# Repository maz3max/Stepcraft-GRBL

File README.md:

# Stepcraft-GRBL
Arduino Uno Shield for Stepcraft GRBL Controller

This is a shield to control STEPCRAFT mills via the LPT port.

(it could be easily modified to work without the LPT module directly plugged into the X1 socket)

An Arduino UNO is used with GRBL firmware and this shield.

The build option USE_SPINDLE_DIR_AS_ENABLE_PIN is needed for GRBL to work with this shield.

It works like a charm on the STEPCRAFT-2/840 with HF500 Spindle attached.

Created with KiCAD, pcb2gcodeGUI and milled on the STEPCRAFT mill itself.

The copyrights of the uploaded manuals are owned by STEPCRAFT.

http://www.netz39.de/

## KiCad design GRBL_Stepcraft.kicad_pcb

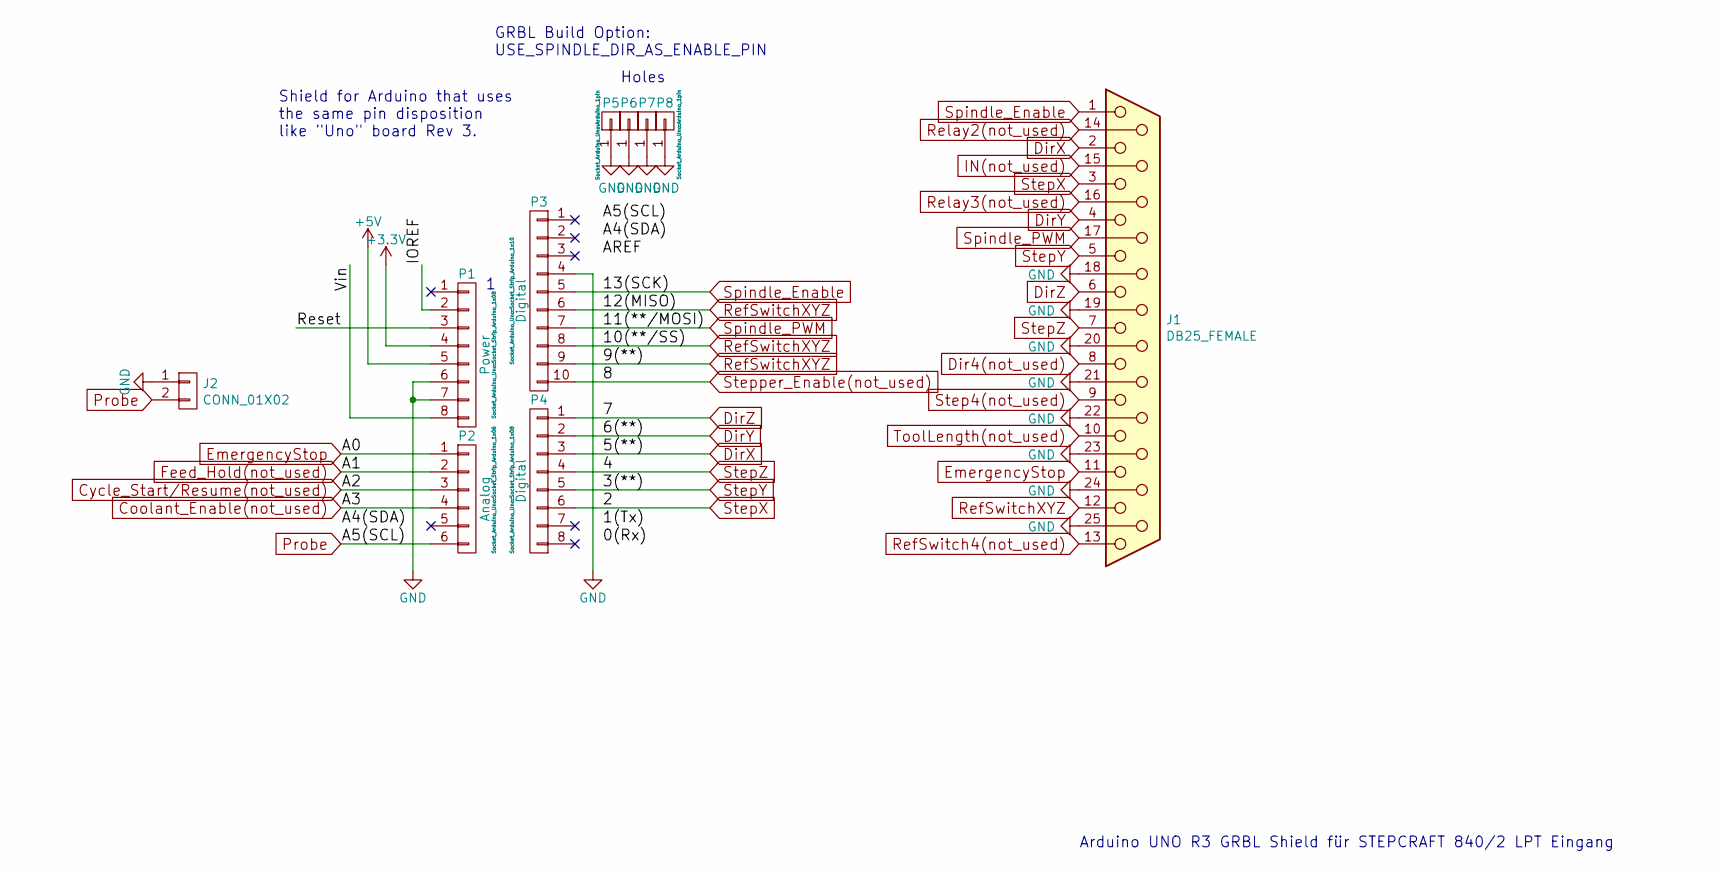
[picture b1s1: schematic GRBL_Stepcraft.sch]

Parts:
J1: DB25_FEMALE; DB25FC
J2: CONN_01X02; Pin_Header_Straight_1x02_Pitch2.54mm
P1: Power; Socket_Strip_Arduino_1x08
P2: Analog; Socket_Strip_Arduino_1x06
P3: Digital; Socket_Strip_Arduino_1x10
P4: Digital; Socket_Strip_Arduino_1x08
P5, P6, P7, P8: CONN_01X01; Arduino_1pin

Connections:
+3V3: P1.4
+5V: P1.5
/IOREF: P1.2
/Reset: P1.3
/Vin: P1.8
Coolant_Enable(not_used): P2.4
Cycle_Start/Resume(not_used): P2.3
Dir4(not_used): J1.8
DirX: J1.2, P4.3
DirY: J1.4, P4.2
DirZ: J1.6, P4.1
EmergencyStop: J1.11, P2.1
Feed_Hold(not_used): P2.2
GND: J1.18, J1.19, J1.20, J1.21, J1.22, J1.23, J1.24, J1.25, J2.1, P1.6, P1.7, P3.4, P5.1, P6.1, P7.1, P8.1
IN(not_used): J1.15
Probe: J2.2, P2.6
RefSwitch4(not_used): J1.13
RefSwitchXYZ: J1.12, P3.6, P3.8, P3.9
Relay2(not_used): J1.14
Relay3(not_used): J1.16
Spindle_Enable: J1.1, P3.5
Spindle_PWM: J1.17, P3.7
Step4(not_used): J1.9
StepX: J1.3, P4.6
StepY: J1.5, P4.5
StepZ: J1.7, P4.4
Stepper_Enable(not_used): P3.10
ToolLength(not_used): J1.10

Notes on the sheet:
Holes
Shield for Arduino that uses the same pin disposition like "Uno" board Rev 3.
GRBL Build Option: USE_SPINDLE_DIR_AS_ENABLE_PIN
Arduino UNO R3 GRBL Shield für STEPCRAFT 840/2 LPT Eingang

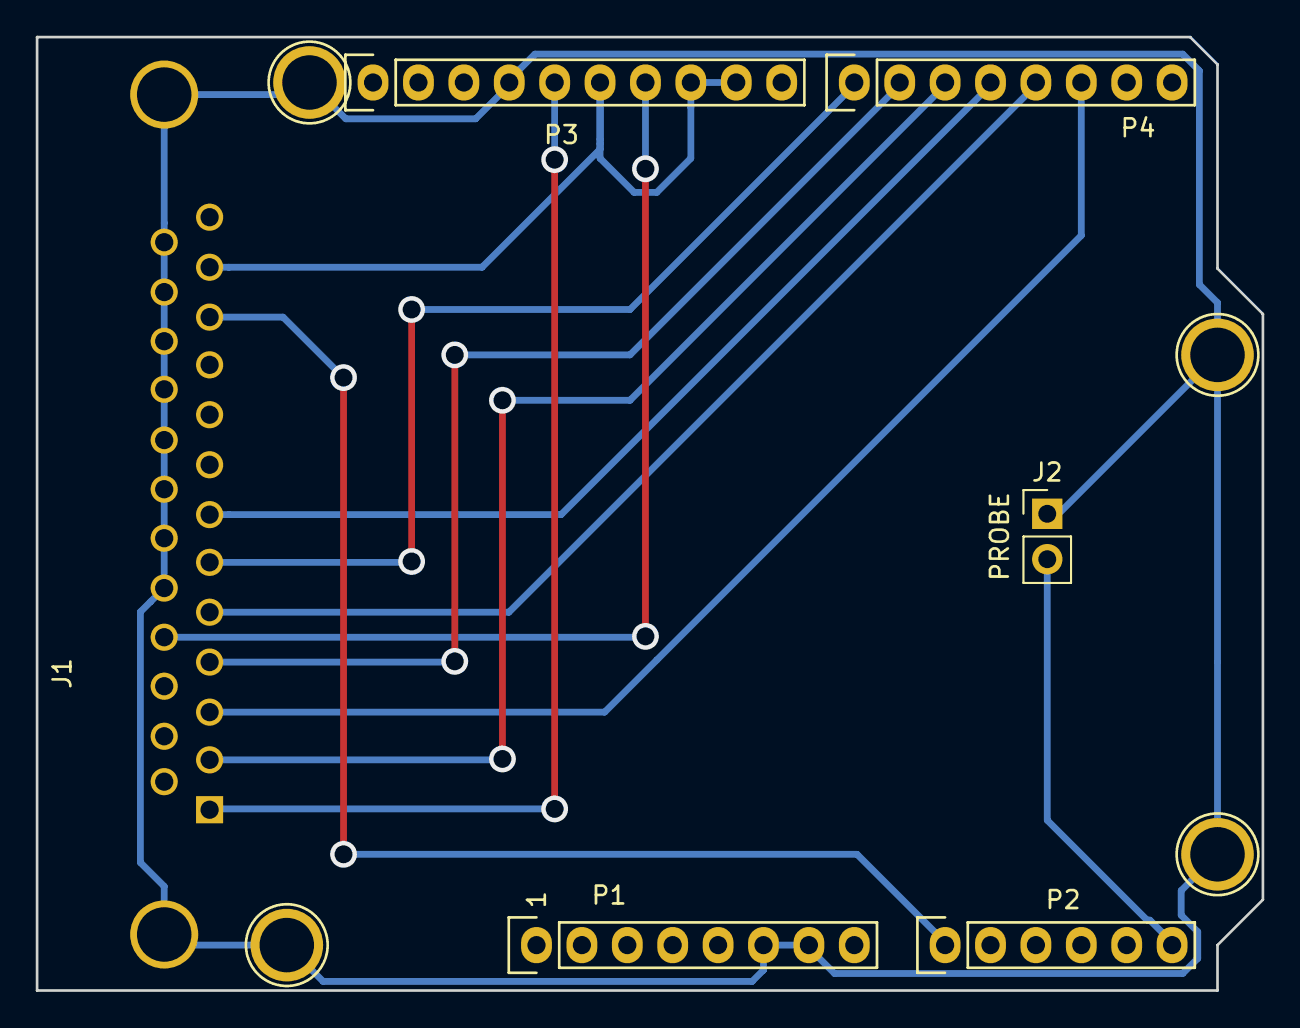
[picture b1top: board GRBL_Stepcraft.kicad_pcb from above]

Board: 2 copper layers, 68.6 x 53.3 mm, 10 parts (0 on the bottom side), 12 nets.

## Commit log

2017-06-12 first working prototype
2017-06-12 brought probe pins to the correct side, tweaked README
2017-06-12 grounded holes
2017-06-12 repositioned components, longer wire brigdes for easier soldering
